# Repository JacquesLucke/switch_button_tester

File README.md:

[Schematic](https://jacqueslucke.github.io/switch_button_tester/switch_button_tester_schematic.pdf)

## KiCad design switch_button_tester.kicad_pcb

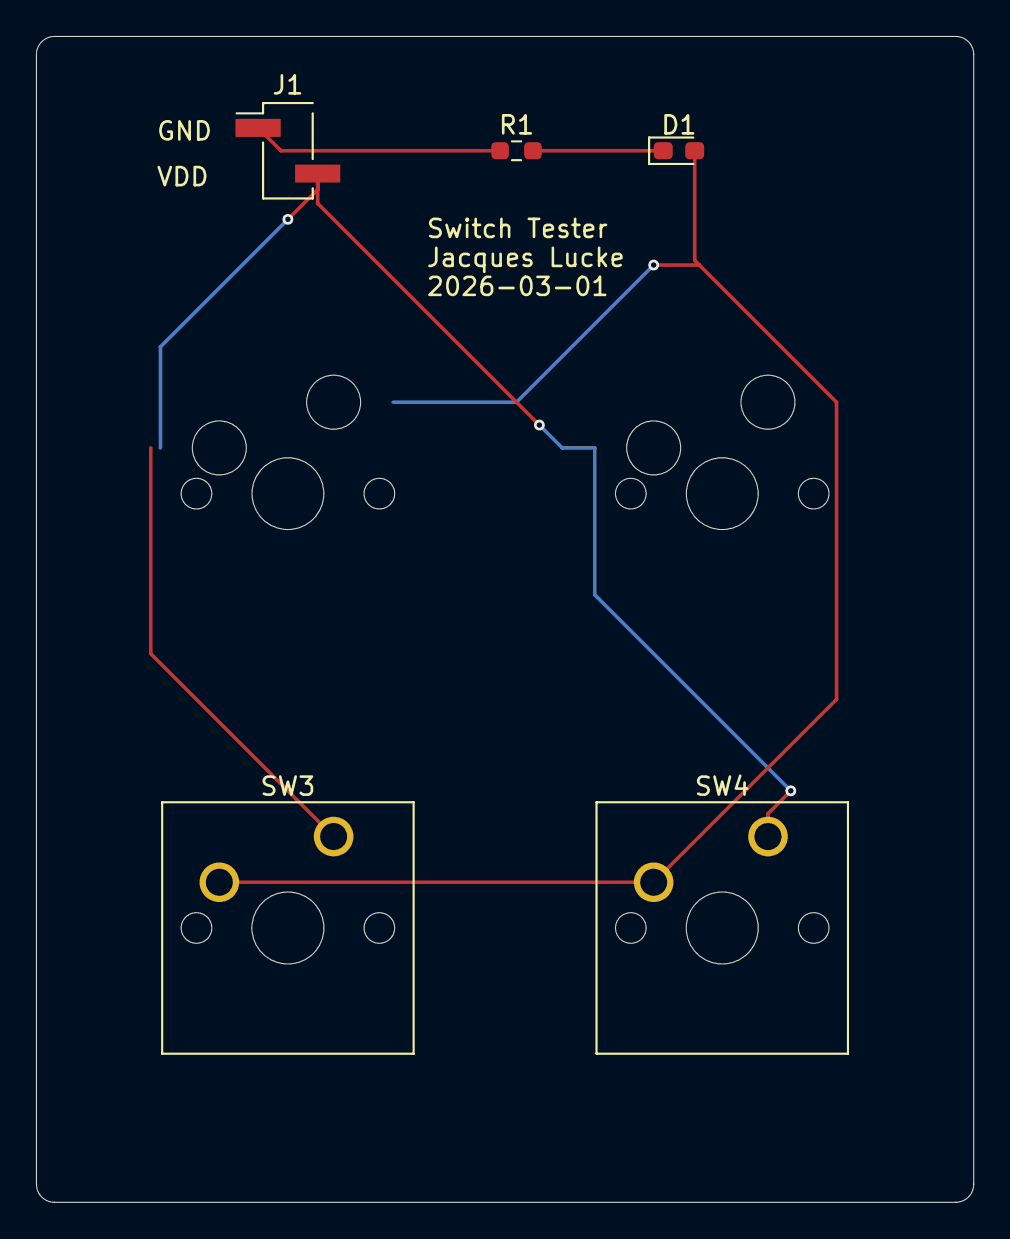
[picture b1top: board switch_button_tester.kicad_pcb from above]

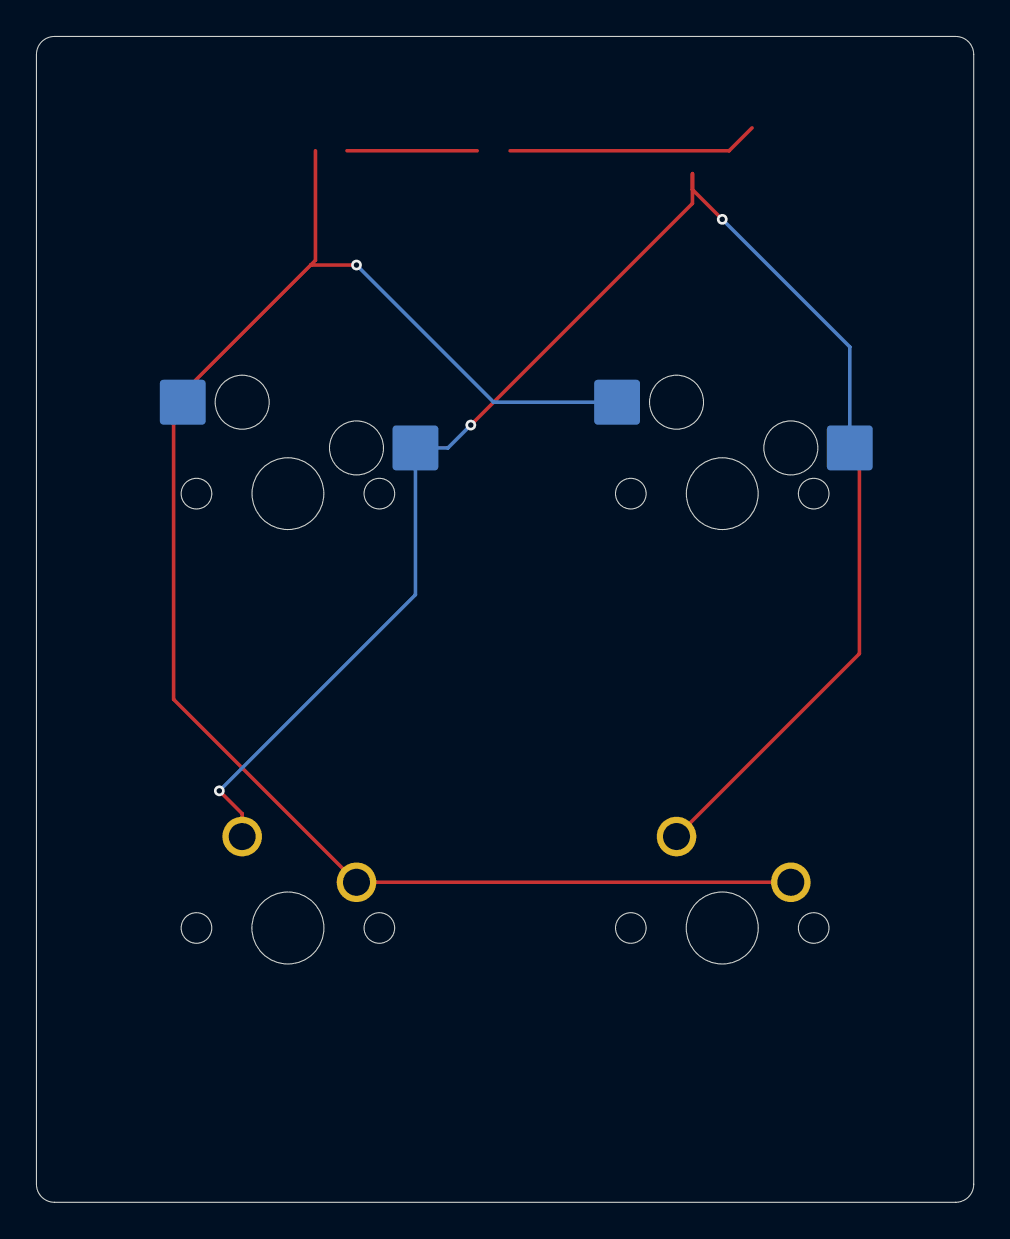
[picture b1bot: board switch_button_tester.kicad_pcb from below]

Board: 2 copper layers, 52.1 x 64.8 mm, 7 parts (2 on the bottom side), 4 nets.

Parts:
D1: LED; LED_0603_1608Metric_Pad1.05x0.95mm_HandSolder
J1: Conn_01x02_Pin; PinHeader_1x02_P2.54mm_Vertical_SMD_Pin1Left
R1: 100; R_0603_1608Metric_Pad0.98x0.95mm_HandSolder
SW1, SW2: SW_Push; MX-Hotswap-1U
SW3, SW4: SW_Push; SW_Cherry_MX_1.00u_PCB

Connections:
unnamed: D1.2 (A), SW1.2, SW2.2, SW3.2, SW4.2
unnamed: D1.1 (K), R1.2
unnamed: J1.1, R1.1
unnamed: J1.2, SW1.1, SW2.1, SW3.1, SW4.1

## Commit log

2026-03-01 add github workflow
2026-03-01 production
2026-03-01 progress
2026-03-01 test
2026-03-01 cleanup
